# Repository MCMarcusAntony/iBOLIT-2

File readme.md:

--------------------------------------------------------------------------------
New iBolit Simple Diagnostics Cartridge version based on previous work done by
the RBSC group.
--------------------------------------------------------------------------------
- Last 16.07.2022 updates included.
- PCB design converted to KiCAD.
- All parts moved to throught hole to help to begginers build.
- Fuses for all voltages on the top slot.
- Connection to a right hand daughter board added.

- Stop'n'go secondary daughter board design added.

Tools added to this board are:
- Logic probe included on Top three pin connector.
- Lighting and acoustic signals to identify HIGH and LOW status.

Code analisys tools (not properly working yet):
- Stop/Go switch the cpu to stop procesing opcodes.
- Step pushbutton to run just an opcode each time.

Development based on Steve Ciarcia design:

--------------------------------------------------------------------------------
iBolit Simple Diagnostics Cartridge
Copyright (c) 2020-2022 RBSC
Last updated: 16.07.2022
--------------------------------------------------------------------------------

UPDATE from 16.07.2022
----------------------

It's recommended to update the cartridge with an overvoltage protection. See the "iBolit_fuse.jpg" image in the Pics folder!

To install the overvoltage protection, isolate pin 24 of IC1 - cut the traces on both sides of the pin. Then purchase and
solder a 5.1V 1W rated zener diode between pins 12 and 24, the cathode should be connected to pin 24. Solder resettable fuse
0.5A between C2 and pin 24 of IC1. Solder a wire between C5 and the cut off trace to supply power to the voltmeters.

This way the PLD ICs and LEDs will be protected from the overvoltage while the 5V voltmeter will show exact voltage on the slot
connector.

About
-----

iBolit is a simple diagnostics cartridge. During the previous years we've seen numerous messages from MSX users, whose computers
suddenly stopped working after being removed from the storage or after another power cycle. Many people complained about black
screens or about total power failure. It's a known fact that RAM and other elements may go bad during storing or at power-on.
Diagnosing those problems usually starts from checking the power rails, clock signals, reset signal's state and activity on data
and address bus. It has been decided to create a simple diagnostics cartridge that could help to perform the initial check of a
computer and rule out the most common problems.

The cartridge that we named "iBolit" ( see Doctor Aybolit) was created using the GAL22V10 programmable logic chips, LED assemblies
and volt/ammeters from the PC's USB socket tester dongles. There's a cartridge slot installed on the top of iBolit cartridge's
board. There one can insert any cartridge including the one with MSX diagnostics ROM (there are a few, but it would be nice to
create a universal one). The GAL firmware is very primitive - if there's a high level on input, the LED connected to the output
will light up. The cartridge is fairly cheap to build - maximum 12-15 Euro - and is relatively easy to assemble. The daughterboard
with voltmeters is detachable.

Where to buy parts
------------------

The parts for assembling the cartridge can be purchased from these sellers on AliExpress:

 - https://www.aliexpress.com/item/32929139598.html   (buy the one with gray case and USB connectors on the left and right side)
 - https://www.aliexpress.com/item/4000078359420.html (buy 2 converters)
 - https://www.aliexpress.com/item/4001336380255.html (buy 2x5 pin headers)
 - https://www.aliexpress.com/item/32890057619.html   (buy 2x5 pin connectors)
 - https://www.aliexpress.com/item/4000970562846.html (also buy blue and yellow colors)
 - https://www.aliexpress.com/item/32800771545.html   (or use a different 5mm LED)
 - https://www.aliexpress.com/item/32918831775.html   (buy 1kOhm SMD resistor assemblies)
 - https://www.aliexpress.com/item/32948284513.html   (this LED is for the -12v voltmeter)
 - https://www.aliexpress.com/item/32375666910.html   (buy 10uF and 47uF capacitors)
 - https://www.aliexpress.com/item/4001146953252.html (buy 50-pin angled slot connector)

Assembling notes
----------------

Please read the following notes carefully:

 - It's highly recommended to install ceramic capacitors everywhere on the board. For the DC-DC converters the ceramic 10uF
   capacitors are a must

 - To adapt the voltmeters to work with iBolit, you need to first carefully open the USB tester's case with a knife and remove
   the board. Then desolder both indicator panels (mark one indicator panel to know where it came from) and desolder both USB
   connectors from the board. After that solder the indicator panels back to the board, but as low as possible. And finally
   solder two 4-pin pin headers to the board, the pins will have to be forces into the board because the distance between the
   holes is not 2.54mm

 - The voltmeter with a separate red LED is for -12v, it should be installed on the lowest position of the daughterboard. See
   the reference images

 - To install a small red LED to the -12v voltmeter (this step is optional), solder the cathode to the upper GND track and
   anode to the second pin from the top. See the reference images. The LED should be a bit above the voltmeter's board

 - Please note that LED assemblies may have incorrect key position! So please always test the LED assemblies with multimeter
   in the diode testing mode to find the correct polarity. The cathode should be on the right, like marked on the board

 - The pins of both DC-DC converters should be carefully bent at 90 degree angle and the converters have to be installed
   face-down. See the reference images

 - The GAL chips need to be programmed with the firmware before use. A widespread TL866 programmer will do just fine. Use
   the .JED firmware file from the "Firmware" folder and the "GAL22V10D" chip type when programming

 - Instead of one blue and two red LED assemblies you might want to install one red and two blue LED assemblies. Make your
   own choice. It's recommended to install the yellow LED assembly at the rightmost position. If you are installing the
   green LED assembly, you need to select a different value for the resistor assembly, for example 330 Ohm instead of 1kOhm

 - Before inserting the diagnostics board into the MSX slot it's highly recommend to make sure that +5v on the slot is within
   acceptable range (not more than 6-7v!), otherwise the diagnostics board may be damaged. The device doesn't have the
   over-voltage protection on the +5v rail

 - The daughterboard with voltmeters is detachable. When it is detached, no power will be supplied to the upper cartridge slot.
   If you need to use the cartridge slot without the attached daughterboard, you need to put 5 jumpers horizontally on 5 pairs
   of pins of the connector

IMPORTANT!
----------

The RBSC provides all the files and information for free, without any liability (see the disclaimer.txt file). The provided information,
software or hardware must not be used for commercial purposes unless permitted by the RBSC. Producing a small amount of bare boards for
personal projects and selling the rest of the batch is allowed without the permission of RBSC.

When the sources of the tools are used to create alternative projects, please always mention the original source and the copyright!

Contact information
-------------------

The members of RBSC group Tnt23, Wierzbowsky, Pencioner, Ptero, GreyWolf, SuperMax and DJS3000 can be contacted via the group's e-mail
address:

info@rbsc.su

The group's coordinator could be reached via this e-mail address:

admin@rbsc.su

The group's website can be found here:

https://rbsc.su/
https://rbsc.su/ru

The RBSC's hardware repository can be found here:

https://github.com/rbsc

The RBSC's 3D model repository can be found here:

https://www.thingiverse.com/groups/rbsc/things

-= ! MSX FOREVER ! =-

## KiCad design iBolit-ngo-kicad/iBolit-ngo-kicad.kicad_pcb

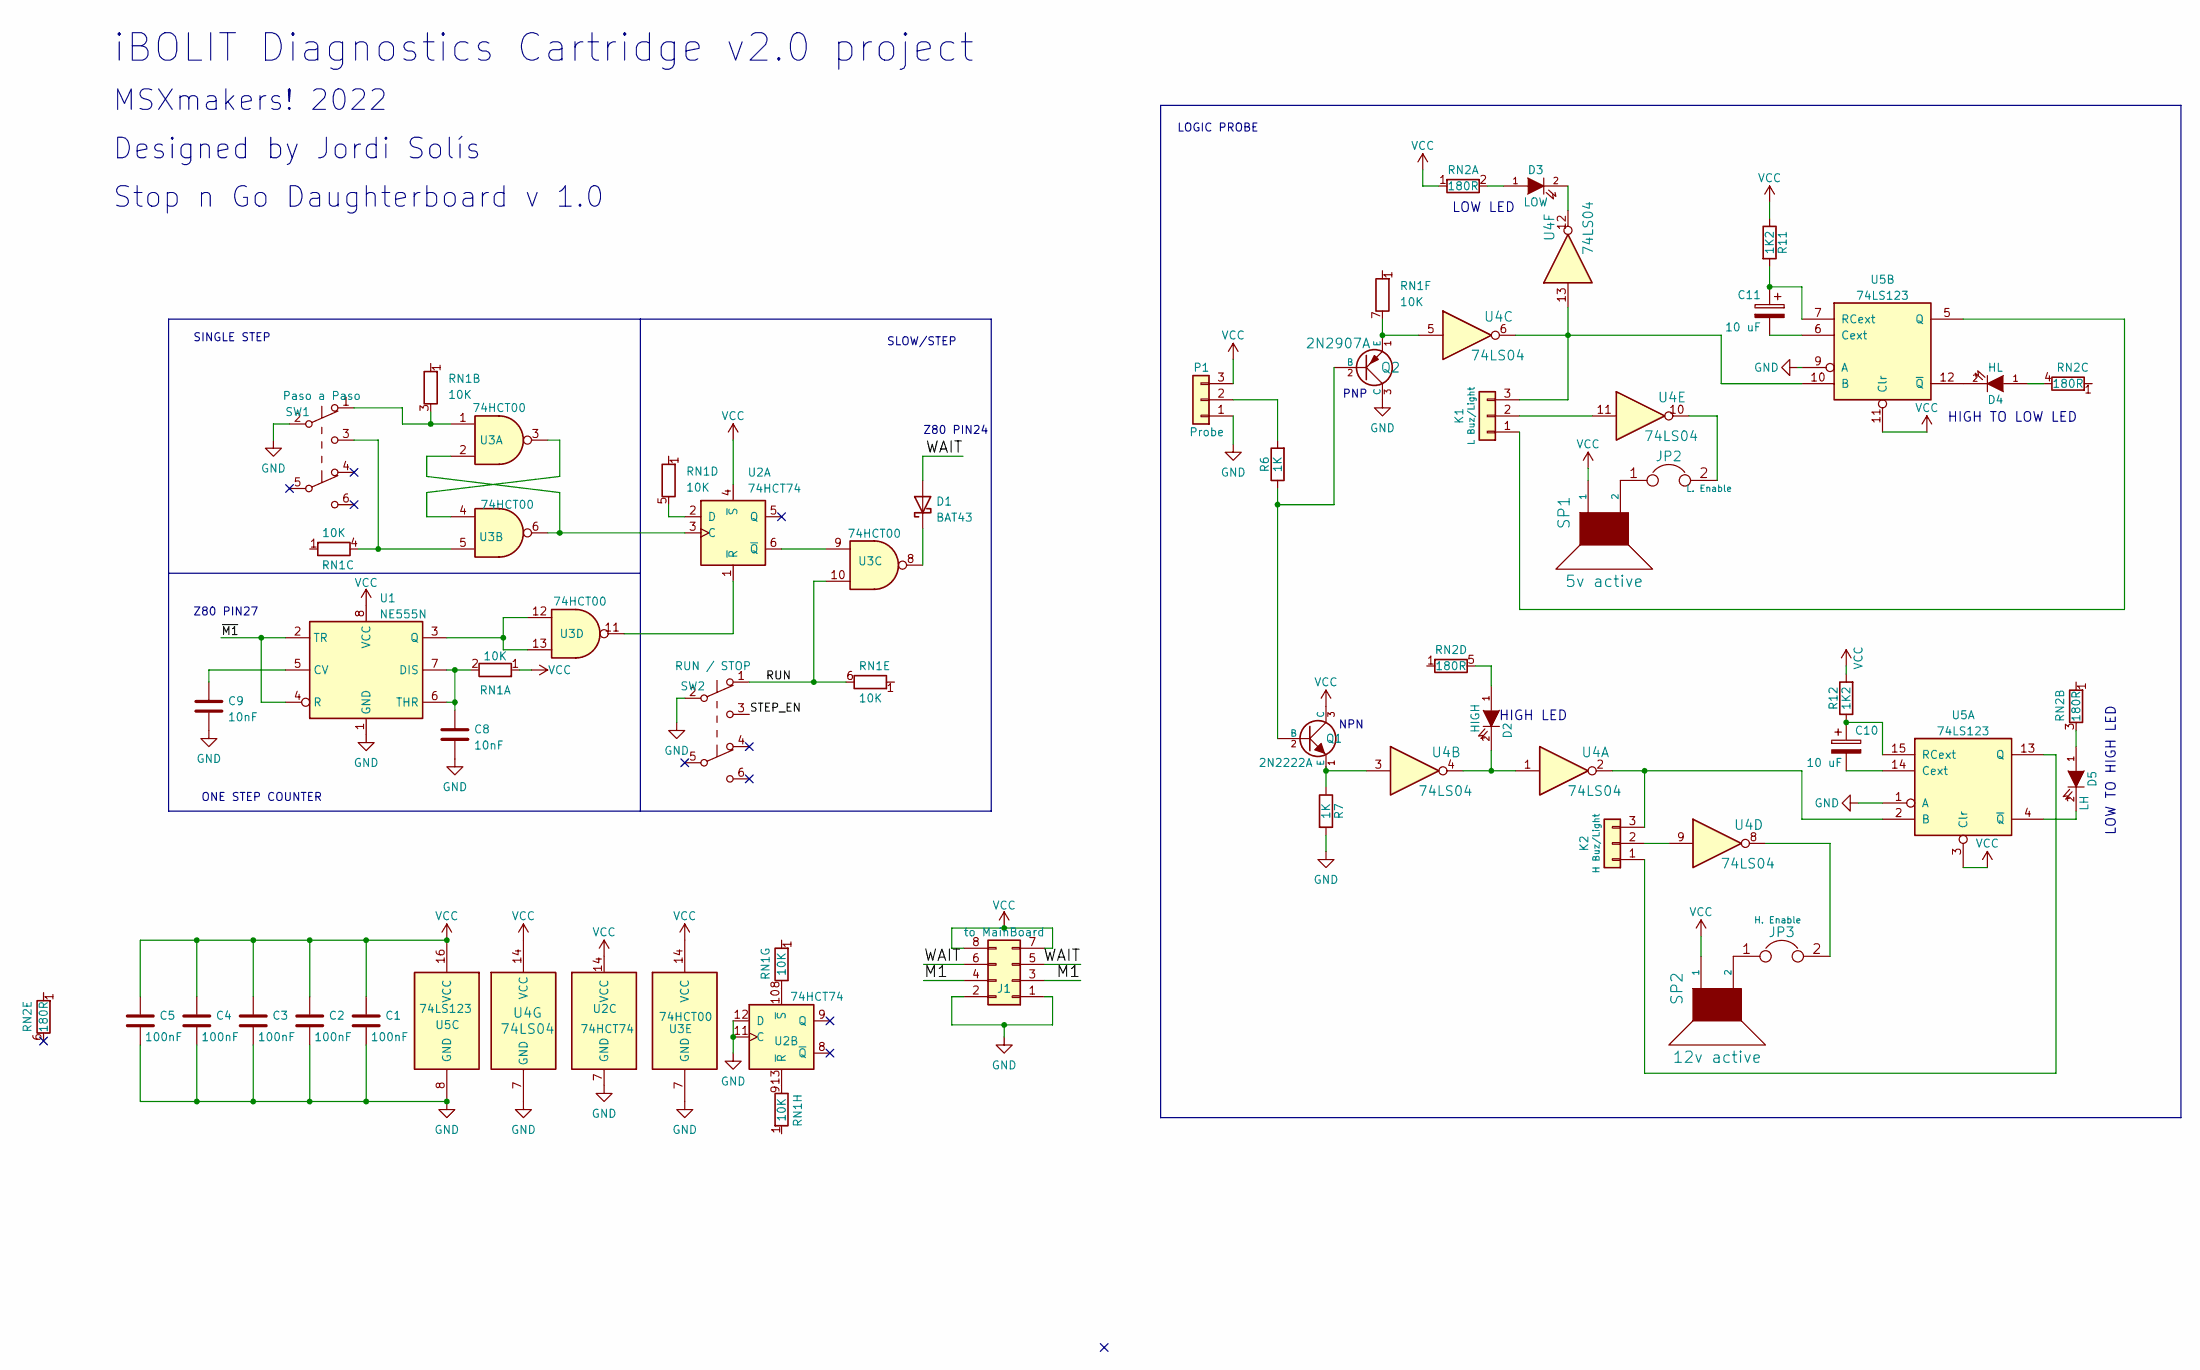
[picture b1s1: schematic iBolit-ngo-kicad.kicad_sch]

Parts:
C1, C2, C3, C4, C5: 100nF; C_Disc_D4.3mm_W1.9mm_P5.00mm
C8, C9: 10nF; C_Disc_D4.3mm_W1.9mm_P5.00mm
C10, C11: 10 uF; CP_Radial_D5.0mm_P2.50mm
D1: BAT43; D_DO-35_SOD27_P7.62mm_Horizontal
D2: HIGH; LED_D3.0mm
D3: LOW; LED_D3.0mm
D4: HL; LED_D3.0mm
D5: LH; LED_D3.0mm
J1: to MainBoard; PinHeader_2x04_P2.54mm_Horizontal
JP2: L. Enable; PinHeader_1x02_P2.54mm_Vertical
JP3: H. Enable; PinHeader_1x02_P2.54mm_Vertical
K1: L Buz/Light; PinHeader_1x03_P2.54mm_Vertical
K2: H Buz/Light; PinHeader_1x03_P2.54mm_Vertical
P1: Probe; PinHeader_1x03_P2.54mm_Vertical
Q1: 2N2222A; TO-92L_Wide
Q2: 2N2907A; TO-92L_Wide
R6, R7: 1K; R_Axial_DIN0207_L6.3mm_D2.5mm_P10.16mm_Horizontal
R11, R12: 1K2; R_Axial_DIN0207_L6.3mm_D2.5mm_P10.16mm_Horizontal
RN1: 10K; R_Array_SIP9
RN2: 180R; R_Array_SIP6
SP1: 5v active; MagneticBuzzer_ProSignal_ABI-009-RC
SP2: 12v active; MagneticBuzzer_ProSignal_ABI-009-RC
SW1: Paso a Paso; SW_Push_2P2T_Toggle_CK_PVA2OAH5xxxxxxV2
SW2: RUN / STOP; SW_Push_2P2T_Toggle_CK_PVA2OAH5xxxxxxV2
U1: NE555N; DIP-8c_W7.62mm_LongPads
U2: 74HCT74; DIP-14c_W7.62mm_LongPads
U3: 74HCT00; DIP-14c_W7.62mm_LongPads
U4: 74LS04; DIP-14c_W7.62mm_LongPads
U5: 74LS123; DIP-16c_W7.62mm_Socket_LongPads

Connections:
/M1: J1.3, J1.4
/RUN: RN1.6 (R5.2), SW1.4 (A), SW2.1 (A), U3.10
/STEP_EN: SW1.5 (B), SW2.3 (C)
/WAIT: D1.2 (A), J1.5, J1.6
/~M1: U1.2 (TR), U1.4 (R)
GND: C1.2, C2.2, C3.2, C4.2, C5.2, C8.2, C9.2, J1.1, J1.2, P1.1, Q2.3 (C), R7.2, SW1.2 (B), SW2.2 (B), U1.1 (GND), U2.7 (GND), U2.11 (C), U2.12 (D), U3.7 (GND), U4.7 (GND), U5.1 (A), U5.8 (GND), U5.9 (A)
unnamed: D1.1 (K), U3.8
unnamed: D2.1 (A), RN2.5 (R4.2)
unnamed: D2.2 (K), U4.1, U4.4
unnamed: D3.1 (A), RN2.2 (R1.2)
unnamed: D3.2 (K), U4.12
unnamed: D4.1 (A), RN2.4 (R3.2)
unnamed: D4.2 (K), U5.12 (~Q)
unnamed: D5.1 (A), RN2.3 (R2.2)
unnamed: D5.2 (K), U5.4 (~Q)
unnamed: JP2.1, SP1.2
unnamed: JP2.2, U4.10
unnamed: JP3.1, SP2.2
unnamed: JP3.2, U4.8
unnamed: K1.1, U5.5 (Q)
unnamed: K1.2, U4.11
unnamed: K1.3, U4.6, U4.13, U5.10 (B)
unnamed: K2.1, U5.13 (Q)
unnamed: K2.2, U4.9
unnamed: K2.3, U4.2, U5.2 (B)
unnamed: P1.2, R6.2
unnamed: Q1.2 (B), Q2.2 (B), R6.1
unnamed: Q1.1 (E), R7.1, U4.3
unnamed: Q2.1 (E), RN1.7 (R6.2), U4.5
unnamed: C8.1, RN1.2 (R1.2), U1.6 (THR), U1.7 (DIS)
unnamed: RN1.3 (R2.2), SW1.1 (A), U3.1
unnamed: RN1.4 (R3.2), SW1.3 (C), U3.5
unnamed: RN1.5 (R4.2), U2.2 (D)
unnamed: C9.1, U1.5 (CV)
unnamed: U1.3 (Q), U3.12, U3.13
unnamed: U2.3 (C), U3.2, U3.6
unnamed: U2.6 (~Q), U3.9
unnamed: U2.1 (~R), U3.11
unnamed: U3.3, U3.4
unnamed: C10.2, U5.14 (Cext)
unnamed: C10.1, R12.1, U5.15 (RCext)
unnamed: C11.2, U5.6 (Cext)
unnamed: C11.1, R11.2, U5.7 (RCext)

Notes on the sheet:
LOGIC PROBE
Stop n Go Daughterboard v 1.0
Designed by Jordi Solís
MSXmakers! 2022
ONE STEP COUNTER
HIGH TO LOW LED
LOW TO HIGH LED
iBOLIT Diagnostics Cartridge v2.0 project
HIGH LED
NPN
Z80 PIN24
SINGLE STEP
LOW LED
PNP
SLOW/STEP
Z80 PIN27

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
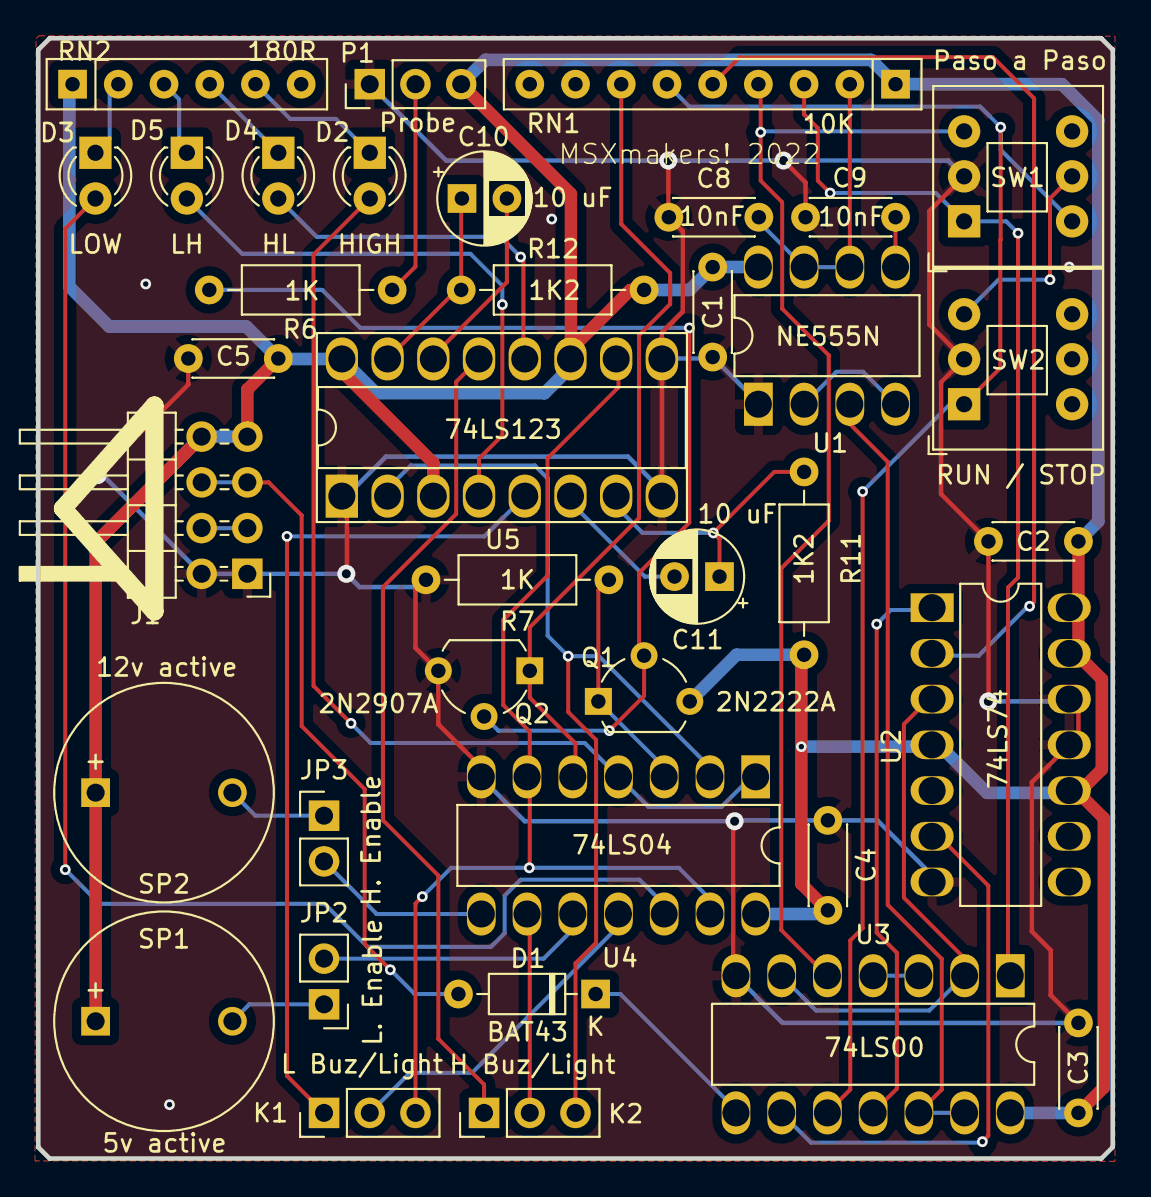
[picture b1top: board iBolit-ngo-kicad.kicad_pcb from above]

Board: 2 copper layers, 59.7 x 62.2 mm, 37 parts (0 on the bottom side), 44 nets.

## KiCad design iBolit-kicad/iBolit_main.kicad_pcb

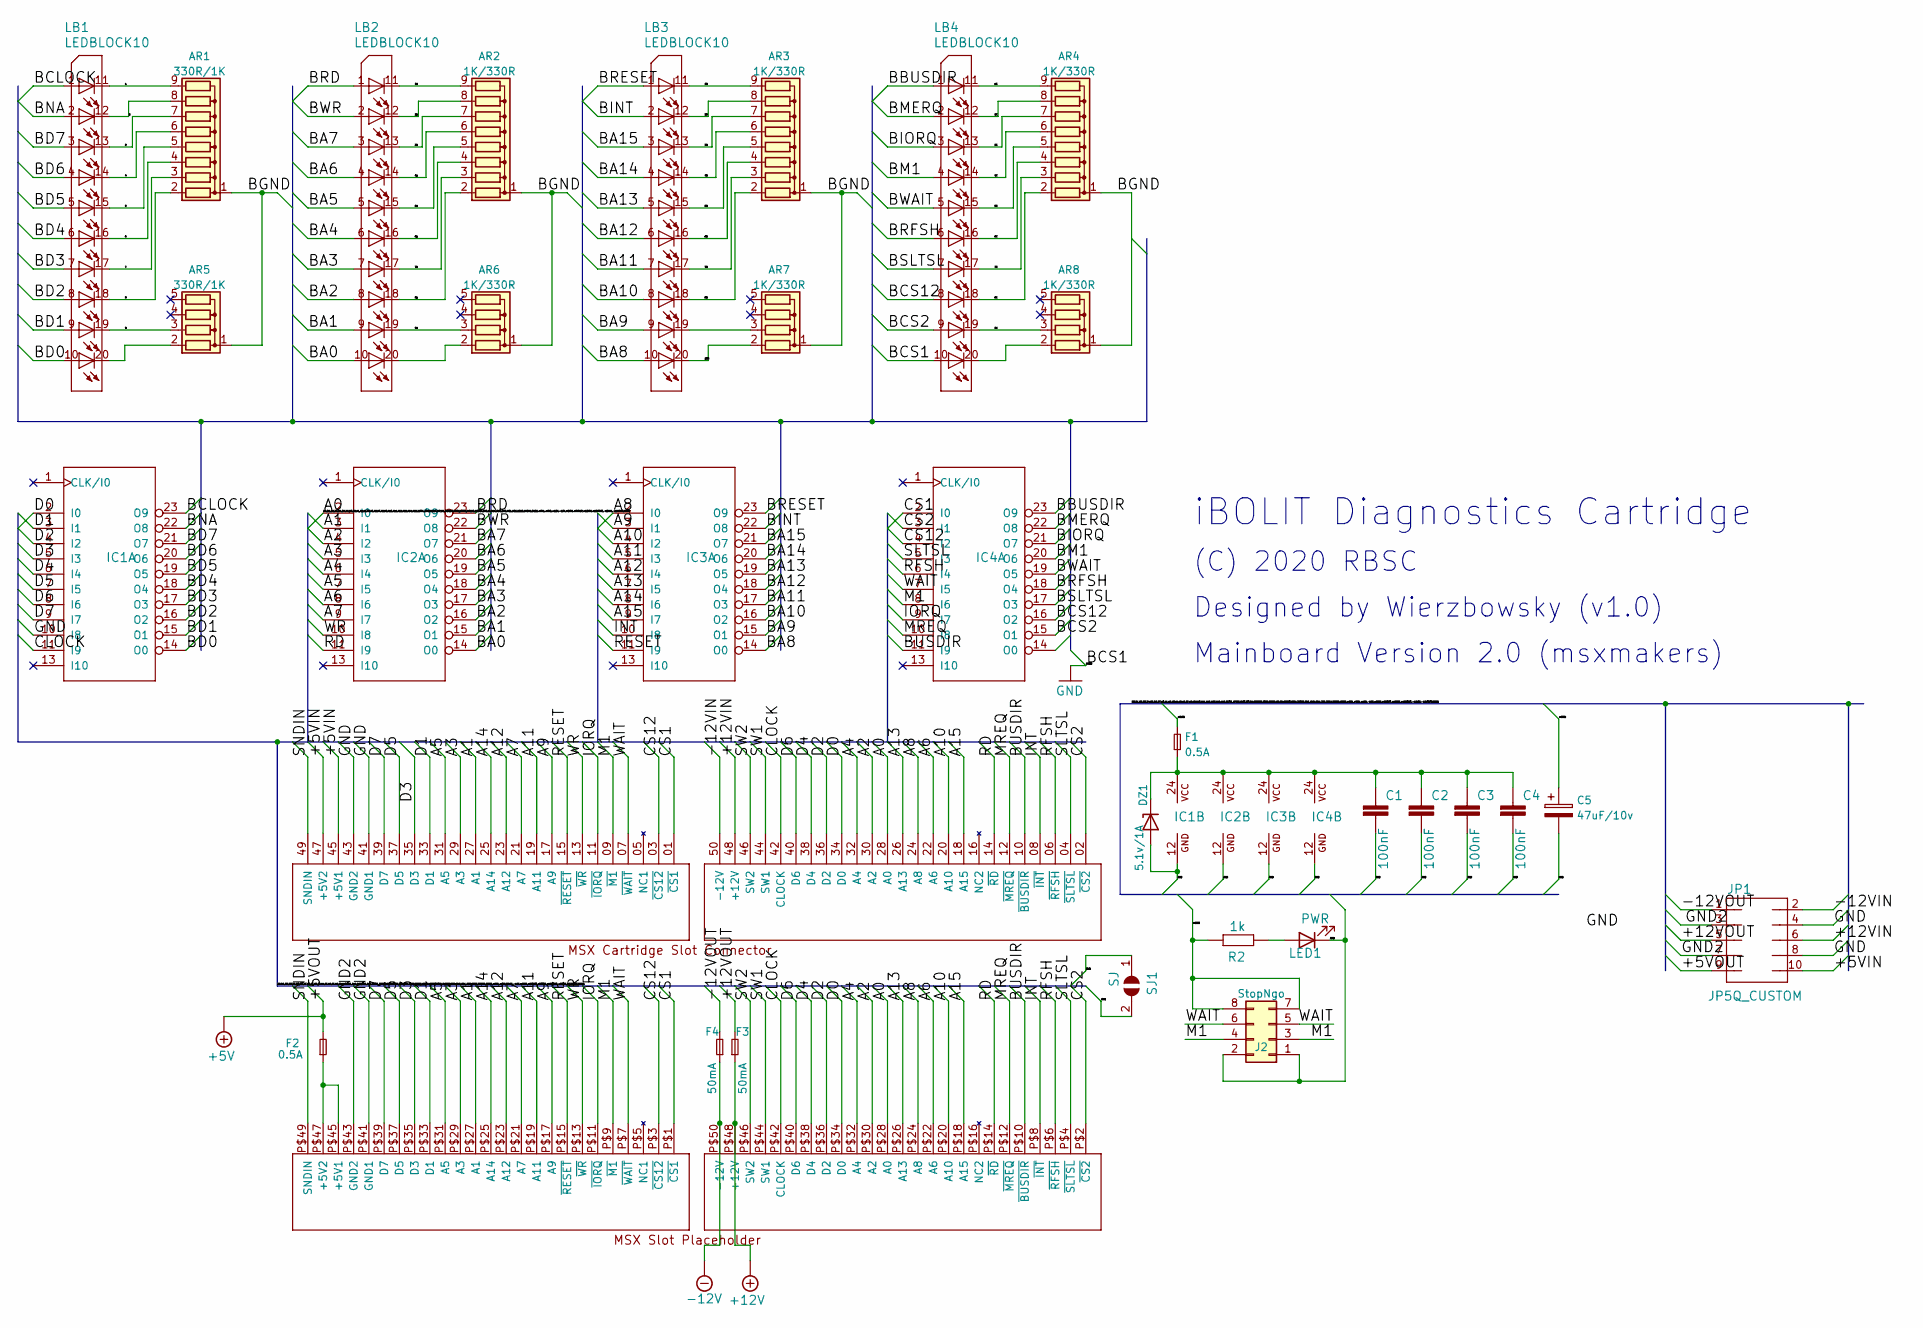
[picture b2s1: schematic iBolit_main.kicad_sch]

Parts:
AR1: 330R/1K; R_Array_SIP9
AR2, AR3, AR4: 1K/330R; R_Array_SIP9
AR5: 330R/1K; R_Array_SIP5
AR6, AR7, AR8: 1K/330R; R_Array_SIP5
C1, C2, C3, C4: 100nF; C_Disc_D4.3mm_W1.9mm_P5.00mm
C5: 47uF/10v; CP_Radial_D6.3mm_P2.50mm
CN1: SLOTCONN; MSX_SLOT_CON
CN2: SLOTPLACEHOLDER; MSX_SLOT_PLP
DZ1: 5.1v/1A; D_DO-41_SOD81_P10.16mm_Horizontal
F1, F2: 0.5A; C_Disc_D5.0mm_W2.5mm_P5.00mm
F3, F4: 50mA; C_Disc_D5.0mm_W2.5mm_P5.00mm
IC1, IC2, IC3, IC4: GAL22V10; DIP-24c_W7.62mm_LongPads
J2: StopNgo; PinSocket_2x04_P2.54mm_Horizontal
JP1: JP5Q_CUSTOM; PinHeader_2x05_P2.54mm_Horizontal
LB1: LEDBLOCK10; HDSP-4832
LB2, LB3: LEDBLOCK10; HDSP-4830
LB4: LEDBLOCK10; HDSP-4850
LED1: PWR; LED_Rectangular_W3.9mm_H1.8mm
R2: 1k; R_Axial_DIN0204_L3.6mm_D1.6mm_P7.62mm_Horizontal
SJ1: SJ; PinHeader_1x02_P2.54mm_Horizontal

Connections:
+5V: F2.2, JP1.9
+12V: CN2.P$48 (+12V), F3.1
-12V: CN2.P$50 (-12V), F4.1
/1: AR1.9 (R8), LB1.11 (L1O)
/1A: AR2.9 (R8), LB2.11 (L1O)
/1B: AR3.9 (R8), LB3.11 (L1O)
/1C: AR4.9 (R8), LB4.11 (L1O)
/2: AR1.8 (R7), LB1.12 (L1O1)
/2A: AR2.8 (R7), LB2.12 (L1O1)
/2B: AR3.8 (R7), LB3.12 (L1O1)
/2C: AR4.8 (R7), LB4.12 (L1O1)
/3: AR1.7 (R6), LB1.13 (L1O2)
/3A: AR2.7 (R6), LB2.13 (L1O2)
/3B: AR3.7 (R6), LB3.13 (L1O2)
/3C: AR4.7 (R6), LB4.13 (L1O2)
/4: AR1.6 (R5), LB1.14 (L1O3)
/4A: AR2.6 (R5), LB2.14 (L1O3)
/4B: AR3.6 (R5), LB3.14 (L1O3)
/4C: AR4.6 (R5), LB4.14 (L1O3)
/5: AR1.5 (R4), LB1.15 (L1O4)
/5A: AR2.5 (R4), LB2.15 (L1O4)
/5B: AR3.5 (R4), LB3.15 (L1O4)
/5C: AR4.5 (R4), LB4.15 (L1O4)
/6: AR1.4 (R3), LB1.16 (L1O5)
/6A: AR2.4 (R3), LB2.16 (L1O5)
/6B: AR3.4 (R3), LB3.16 (L1O5)
/6C: AR4.4 (R3), LB4.16 (L1O5)
/7: AR1.3 (R2), LB1.17 (L1O6)
/7A: AR2.3 (R2), LB2.17 (L1O6)
/7B: AR3.3 (R2), LB3.17 (L1O6)
/7C: AR4.3 (R2), LB4.17 (L1O6)
/8: AR1.2 (R1), LB1.18 (L1O7)
/8A: AR2.2 (R1), LB2.18 (L1O7)
/8B: AR3.2 (R1), LB3.18 (L1O7)
/8C: AR4.2 (R1), LB4.18 (L1O7)
/9: AR5.3 (R2), LB1.19 (L1O8)
/9A: AR6.3 (R2), LB2.19 (L1O8)
/9C: AR8.3 (R2), LB4.19 (L1O8)
/10B: AR7.2 (R1), LB3.20 (L1O9)
/+5VIN: C5.1, CN1.45 (+5V1), CN1.47 (+5V2), F1.2, J2.7, J2.8, JP1.10, R2.2
/+12VIN: CN1.48 (+12V), JP1.6
/+12VOUT: F3.2, JP1.5
/-12VIN: CN1.50 (-12V), JP1.2
/-12VOUT: F4.2, JP1.1
/A0: CN1.28 (A0), CN2.P$28 (A0), IC2.2 (I0)
/A1: CN1.27 (A1), CN2.P$27 (A1), IC2.3 (I1)
/A2: CN1.30 (A2), CN2.P$30 (A2), IC2.4 (I2)
/A3: CN1.29 (A3), CN2.P$29 (A3), IC2.5 (I3)
/A4: CN1.32 (A4), CN2.P$32 (A4), IC2.6 (I4)
/A5: CN1.31 (A5), CN2.P$31 (A5), IC2.7 (I5)
/A6: CN1.22 (A6), CN2.P$22 (A6), IC2.8 (I6)
/A7: CN1.21 (A7), CN2.P$21 (A7), IC2.9 (I7)
/A8: CN1.24 (A8), CN2.P$24 (A8), IC3.2 (I0)
/A9: CN1.17 (A9), CN2.P$17 (A9), IC3.3 (I1)
/A10: CN1.20 (A10), CN2.P$20 (A10), IC3.4 (I2)
/A11: CN1.19 (A11), CN2.P$19 (A11), IC3.5 (I3)
/A12: CN1.23 (A12), CN2.P$23 (A12), IC3.6 (I4)
/A13: CN1.26 (A13), CN2.P$26 (A13), IC3.7 (I5)
/A14: CN1.25 (A14), CN2.P$25 (A14), IC3.8 (I6)
/A15: CN1.18 (A15), CN2.P$18 (A15), IC3.9 (I7)
/BA0: IC2.14 (O0), LB2.10 (L1I9)
/BA1: IC2.15 (O1), LB2.9 (L1I8)
/BA2: IC2.16 (O2), LB2.8 (L1I7)
/BA3: IC2.17 (O3), LB2.7 (L1I6)
/BA4: IC2.18 (O4), LB2.6 (L1I5)
/BA5: IC2.19 (O5), LB2.5 (L1I4)
/BA6: IC2.20 (O6), LB2.4 (L1I3)
/BA7: IC2.21 (O7), LB2.3 (L1I2)
/BA8: IC3.14 (O0), LB3.10 (L1I9)
/BA9: IC3.15 (O1), LB3.9 (L1I8)
/BA10: IC3.16 (O2), LB3.8 (L1I7)
/BA11: IC3.17 (O3), LB3.7 (L1I6)
/BA12: IC3.18 (O4), LB3.6 (L1I5)
/BA13: IC3.19 (O5), LB3.5 (L1I4)
/BA14: IC3.20 (O6), LB3.4 (L1I3)
/BA15: IC3.21 (O7), LB3.3 (L1I2)
/BBUSDIR: IC4.23 (O9), LB4.1 (L1I)
/BCLOCK: IC1.23 (O9), LB1.1 (L1I)
/BCS2: IC4.15 (O1), LB4.9 (L1I8)
/BCS12: IC4.16 (O2), LB4.8 (L1I7)
/BD0: IC1.14 (O0), LB1.10 (L1I9)
/BD1: IC1.15 (O1), LB1.9 (L1I8)
/BD2: IC1.16 (O2), LB1.8 (L1I7)
/BD3: IC1.17 (O3), LB1.7 (L1I6)
/BD4: IC1.18 (O4), LB1.6 (L1I5)
/BD5: IC1.19 (O5), LB1.5 (L1I4)
/BD6: IC1.20 (O6), LB1.4 (L1I3)
/BD7: IC1.21 (O7), LB1.3 (L1I2)
/BINT: IC3.22 (O8), LB3.2 (L1I1)
/BIORQ: IC4.21 (O7), LB4.3 (L1I2)
/BM1: IC4.20 (O6), LB4.4 (L1I3)
/BMERQ: IC4.22 (O8), LB4.2 (L1I1)
/BNA: IC1.22 (O8), LB1.2 (L1I1)
/BRD: IC2.23 (O9), LB2.1 (L1I)
/BRESET: IC3.23 (O9), LB3.1 (L1I)
/BRFSH: IC4.18 (O4), LB4.6 (L1I5)
/BSLTSL: IC4.17 (O3), LB4.7 (L1I6)
/BUSDIR: CN1.10 (~BUSDIR), CN2.P$10 (~BUSDIR), IC4.11 (I9)
/BWAIT: IC4.19 (O5), LB4.5 (L1I4)
/BWR: IC2.22 (O8), LB2.2 (L1I1)
/CLOCK: CN1.42 (CLOCK), CN2.P$42 (CLOCK), IC1.11 (I9)
/CS1: CN1.01 (~CS1), CN2.P$1 (~CS1), IC4.2 (I0)
/CS2: CN1.02 (~CS2), CN2.P$2 (~CS2), IC4.3 (I1)
/CS12: CN1.03 (~CS12), CN2.P$3 (~CS12), IC4.4 (I2)
/D0: CN1.34 (D0), CN2.P$34 (D0), IC1.2 (I0)
/D1: CN1.33 (D1), CN2.P$33 (D1), IC1.3 (I1)
/D2: CN1.36 (D2), CN2.P$36 (D2), IC1.4 (I2)
/D3: CN1.35 (D3), CN2.P$35 (D3), IC1.5 (I3)
/D4: CN1.38 (D4), CN2.P$38 (D4), IC1.6 (I4)
/D5: CN1.37 (D5), CN2.P$37 (D5), IC1.7 (I5)
/D6: CN1.40 (D6), CN2.P$40 (D6), IC1.8 (I6)
/D7: CN1.39 (D7), CN2.P$39 (D7), IC1.9 (I7)
/GND2: CN2.P$41 (GND1), CN2.P$43 (GND2), JP1.3, JP1.7
/INT: CN1.08 (~INT), CN2.P$8 (~INT), IC3.10 (I8)
/IORQ: CN1.11 (~IORQ), CN2.P$11 (~IORQ), IC4.9 (I7)
/M1: CN1.09 (~M1), CN2.P$9 (~M1), IC4.8 (I6), J2.3, J2.4
/MREQ: CN1.12 (~MREQ), CN2.P$12 (~MREQ), IC4.10 (I8)
/RD: CN1.14 (~RD), CN2.P$14 (~RD), IC2.11 (I9)
/RESET: CN1.15 (~RESET), CN2.P$15 (~RESET), IC3.11 (I9)
/RFSH: CN1.06 (~RFSH), CN2.P$6 (~RFSH), IC4.6 (I4)
/SLTSL: CN1.04 (~SLTSL), CN2.P$4 (~SLTSL), IC4.5 (I3)
/SNDIN: CN1.49 (SNDIN), CN2.P$49 (SNDIN)
/SW1: CN1.44 (SW1), CN2.P$44 (SW1), SJ1.2
/SW2: CN1.46 (SW2), CN2.P$46 (SW2), SJ1.1
/WAIT: CN1.07 (~WAIT), CN2.P$7 (~WAIT), IC4.7 (I5), J2.5, J2.6
/WR: CN1.13 (~WR), CN2.P$13 (~WR), IC2.10 (I8)
GND: AR1.1 (common), AR2.1 (common), AR3.1 (common), AR4.1 (common), AR5.1 (common), AR6.1 (common), AR7.1 (common), AR8.1 (common), C1.2, C2.2, C3.2, C4.2, C5.2, CN1.41 (GND1), CN1.43 (GND2), DZ1.2 (A), IC1.10 (I8), IC1.12 (GND), IC2.12 (GND), IC3.12 (GND), IC4.12 (GND), J2.1, J2.2, JP1.4, JP1.8, LB4.10 (L1I9), LED1.1 (K)
unnamed: AR5.2 (R1), LB1.20 (L1O9)
unnamed: AR6.2 (R1), LB2.20 (L1O9)
unnamed: AR7.3 (R2), LB3.19 (L1O8)
unnamed: AR8.2 (R1), LB4.20 (L1O9)
unnamed: C1.1, C2.1, C3.1, C4.1, DZ1.1 (K), F1.1, IC1.24 (VCC), IC2.24 (VCC), IC3.24 (VCC), IC4.24 (VCC)
unnamed: CN2.P$45 (+5V1), CN2.P$47 (+5V2), F2.1
unnamed: LED1.2 (A), R2.1

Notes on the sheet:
(C) 2020 RBSC
Mainboard Version 2.0 (msxmakers)
Designed by Wierzbowsky (v1.0)
iBOLIT Diagnostics Cartridge

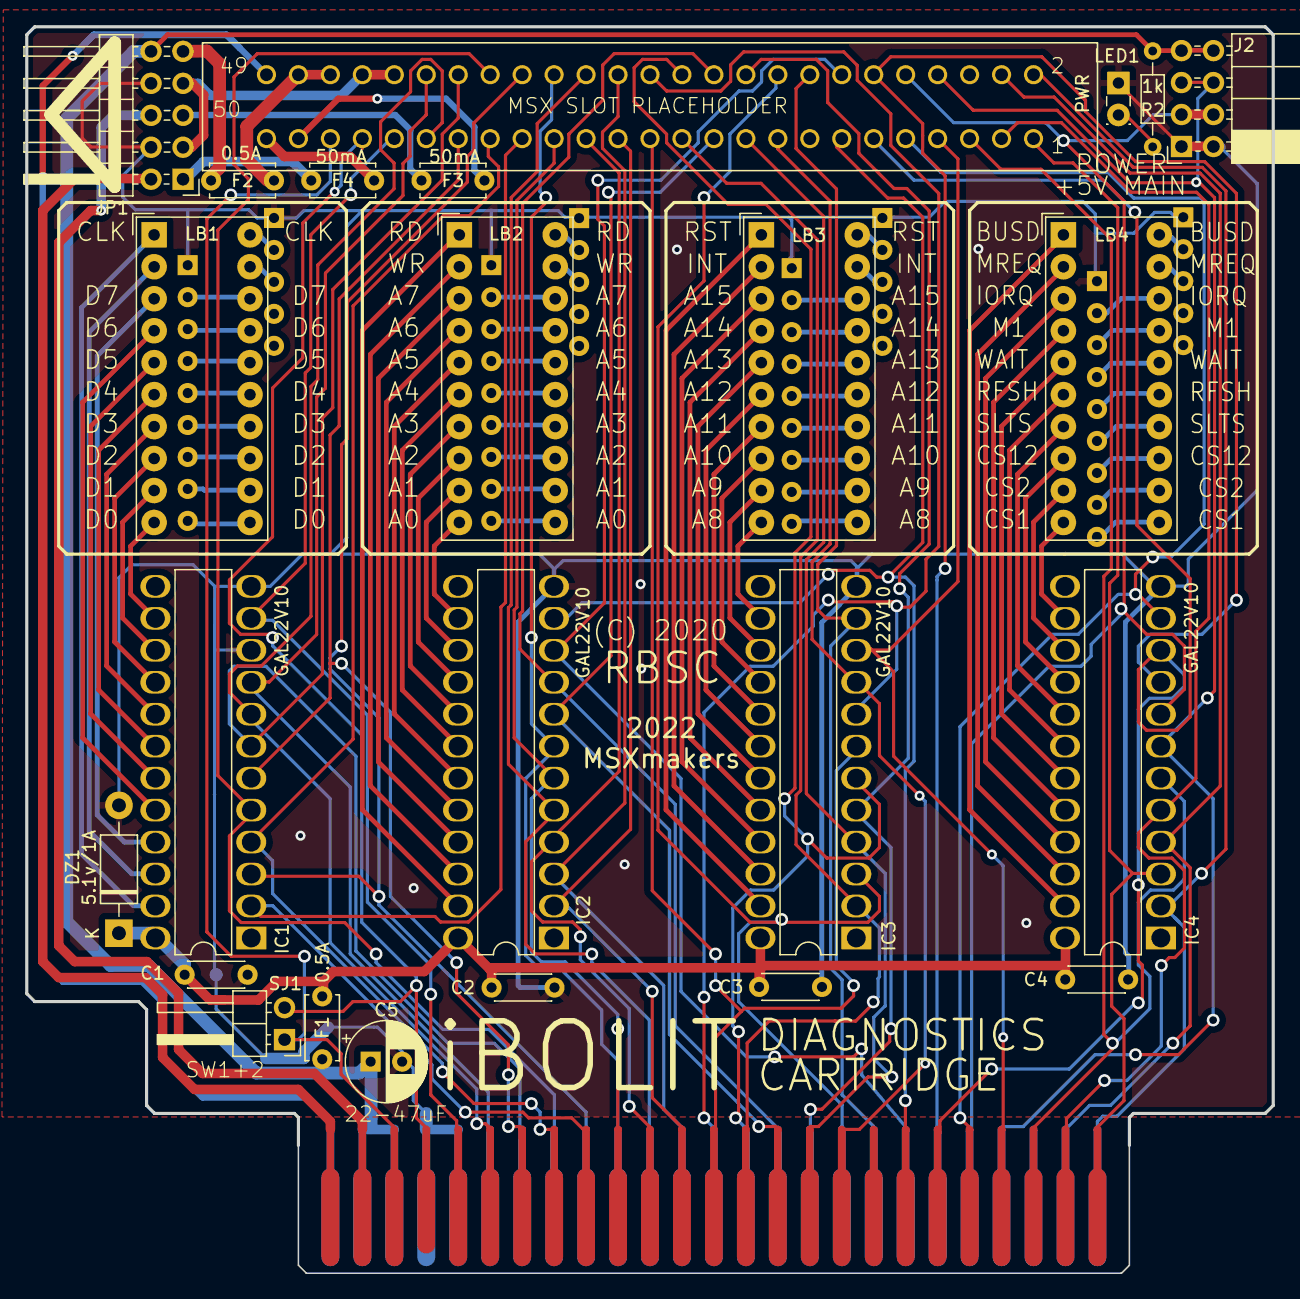
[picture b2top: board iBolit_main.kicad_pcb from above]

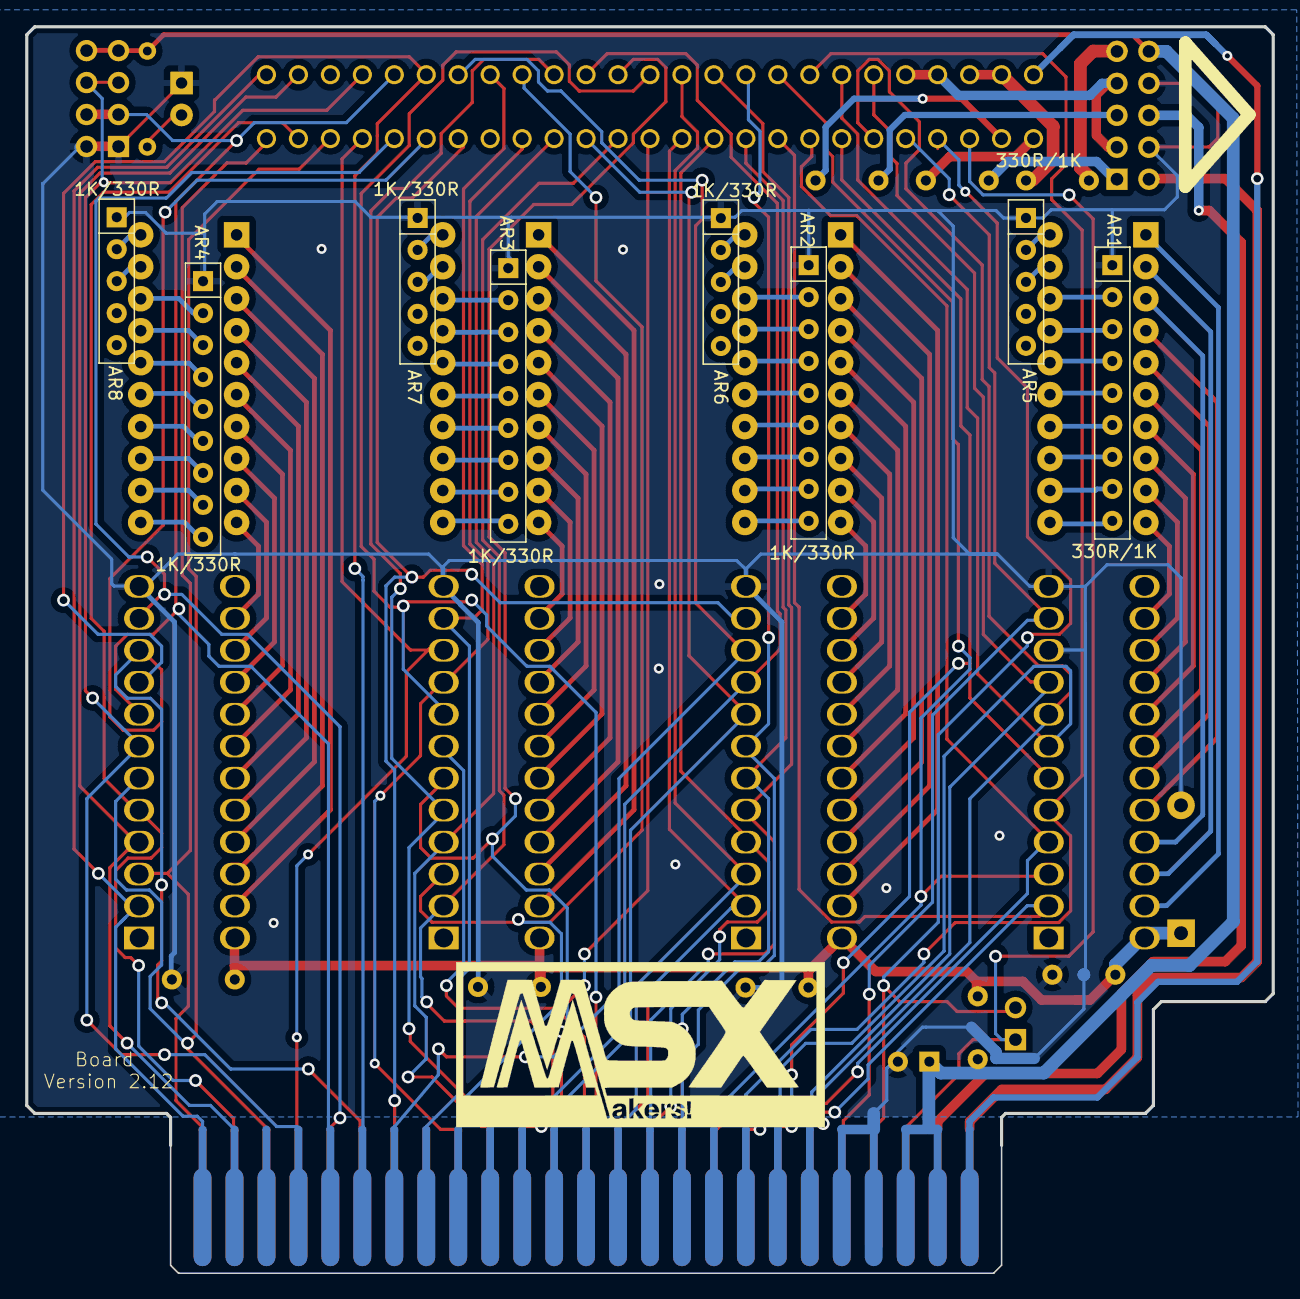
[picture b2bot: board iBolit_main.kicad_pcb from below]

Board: 2 copper layers, 99.1 x 99.1 mm, 33 parts (8 on the bottom side), 134 nets.

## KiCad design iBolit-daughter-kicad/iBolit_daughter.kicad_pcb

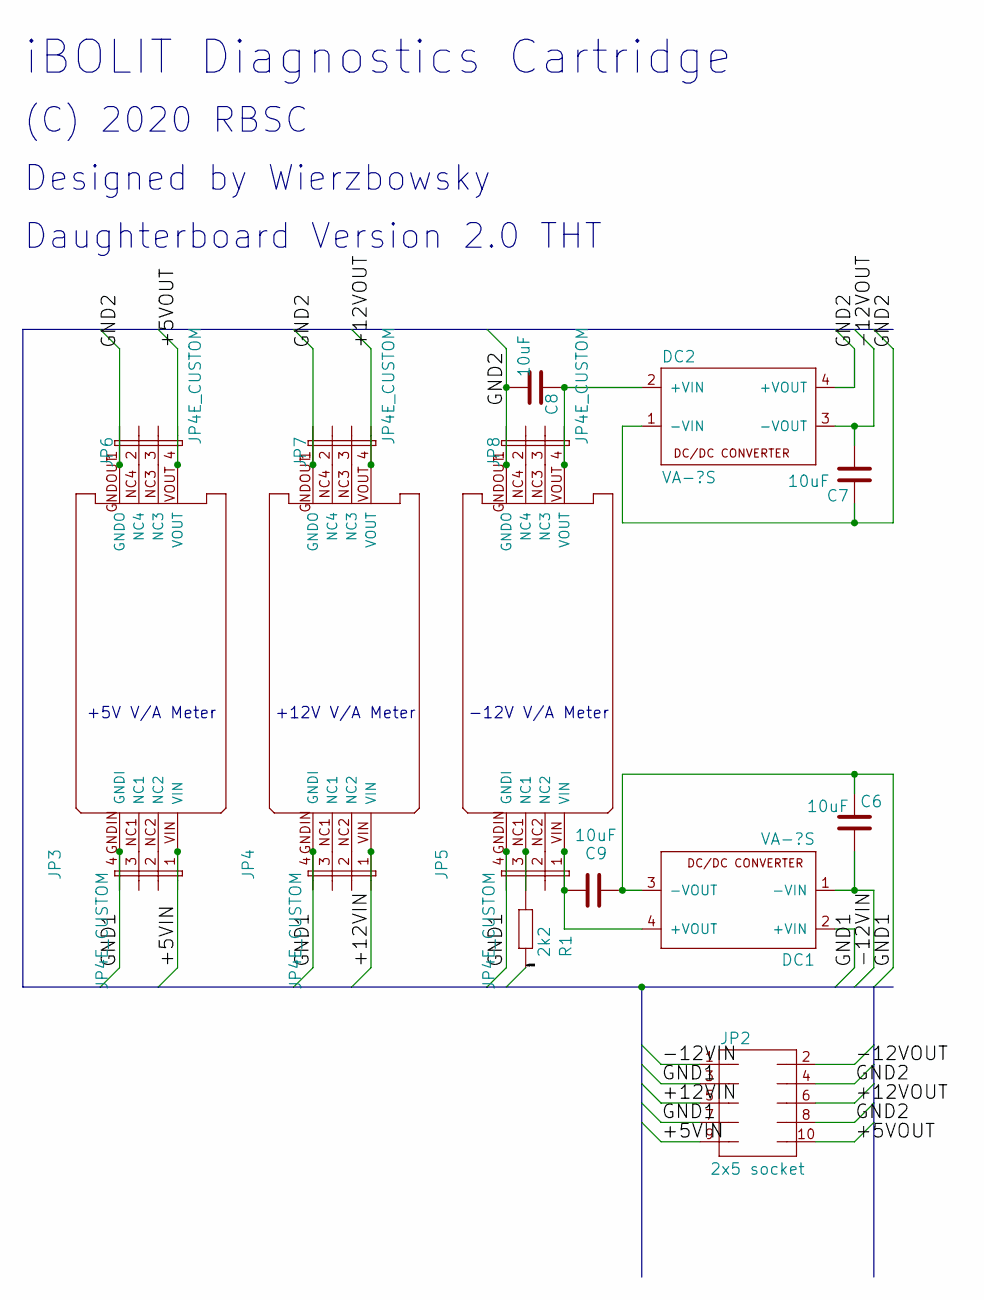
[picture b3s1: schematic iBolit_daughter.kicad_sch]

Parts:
C6, C7, C8, C9: 10uF; C_Disc_D4.7mm_W2.5mm_P5.00mm
DC1, DC2: VA-?S; 4SIL
JP2: 2x5 socket; JP5Q_CUSTOM
JP3, JP4, JP5, JP6, JP7, JP8: JP4E_CUSTOM; JP4_CUSTOM
R1: 2k2; R_Axial_DIN0207_L6.3mm_D2.5mm_P7.62mm_Horizontal
X1, X2, X3: VA-METER; VA_METER

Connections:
/+5VIN: JP2.9, JP3.1, R1.1, X1.VIN
/+5VOUT: JP2.10, JP6.4, X1.VOUT
/+12VIN: JP2.5, JP4.1, X2.VIN
/+12VOUT: JP2.6, JP7.4, X2.VOUT
/-12VIN: C6.2, DC1.1 (-VIN), JP2.1
/-12VOUT: C7.2, DC2.3 (-VOUT), JP2.2
/GND1: C6.1, C9.2, DC1.2 (+VIN), DC1.3 (-VOUT), JP2.3, JP2.7, JP3.4, JP4.4, JP5.4, X1.GNDIN (GNDI), X2.GNDIN (GNDI), X3.GNDIN (GNDI)
/GND2: C7.1, C8.2, DC2.1 (-VIN), DC2.4 (+VOUT), JP2.4, JP2.8, JP6.1, JP7.1, JP8.1, X1.GNDOUT (GNDO), X2.GNDOUT (GNDO), X3.GNDOUT (GNDO)
unnamed: C8.1, DC2.2 (+VIN), JP8.4, X3.VOUT
unnamed: JP3.2, X1.NC2
unnamed: JP3.3, X1.NC1
unnamed: JP4.2, X2.NC2
unnamed: JP4.3, X2.NC1
unnamed: C9.1, DC1.4 (+VOUT), JP5.1, X3.VIN
unnamed: JP5.2, X3.NC2
unnamed: JP5.3, R1.2, X3.NC1
unnamed: JP6.2, X1.NC4
unnamed: JP6.3, X1.NC3
unnamed: JP7.2, X2.NC4
unnamed: JP7.3, X2.NC3
unnamed: JP8.2, X3.NC4
unnamed: JP8.3, X3.NC3

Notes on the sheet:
iBOLIT Diagnostics Cartridge
Daughterboard Version 2.0 THT
+12V V/A Meter
+5V V/A Meter
(C) 2020 RBSC
Designed by Wierzbowsky
-12V V/A Meter

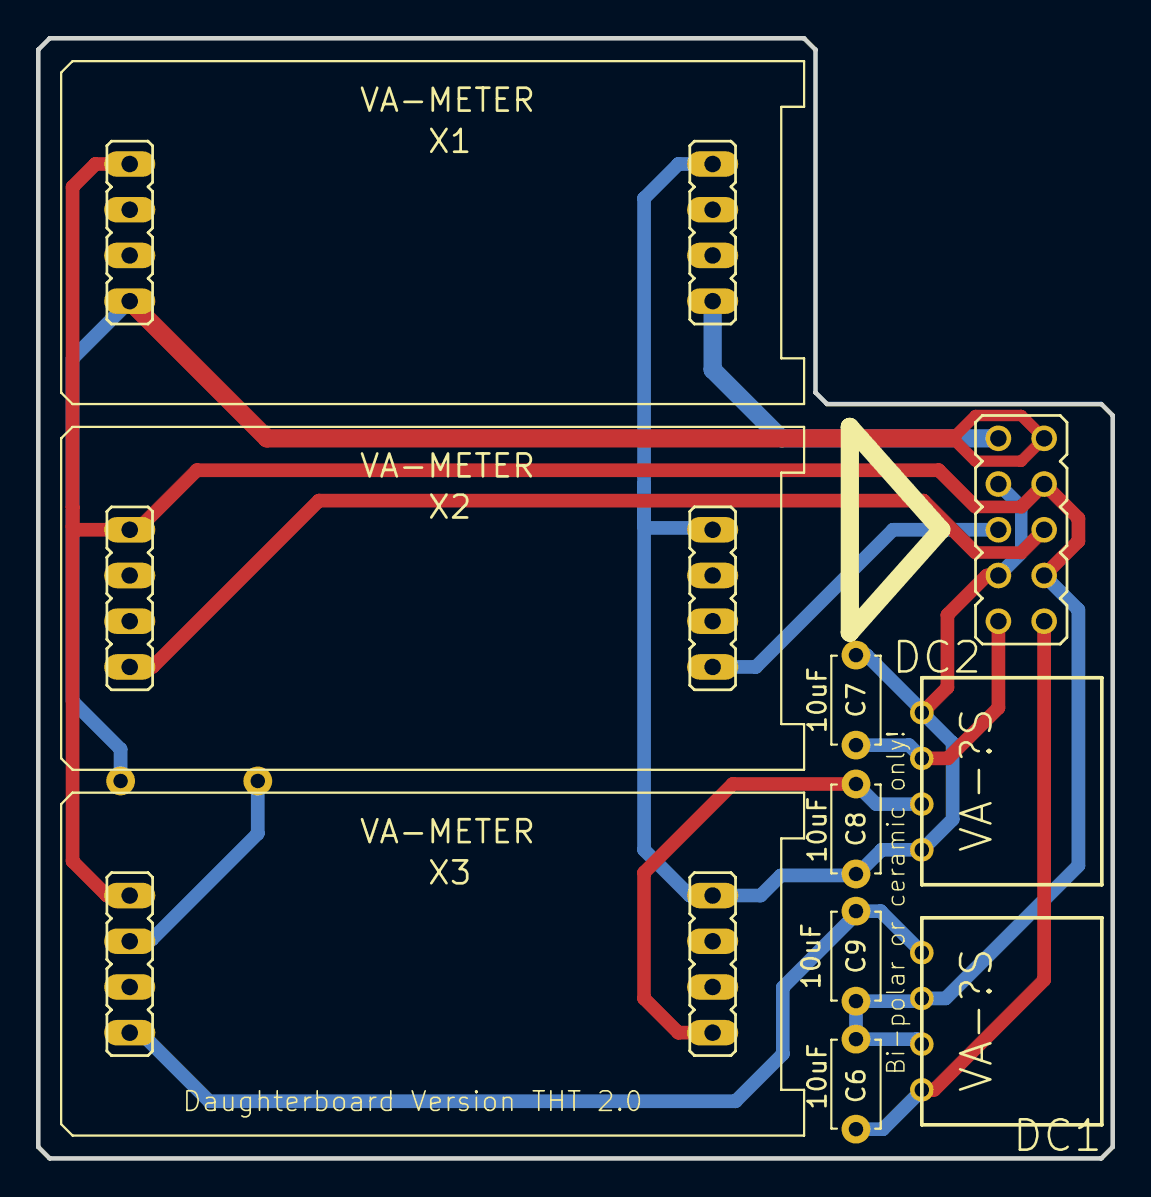
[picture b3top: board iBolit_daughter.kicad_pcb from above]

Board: 2 copper layers, 59.7 x 62.2 mm, 17 parts (1 on the bottom side), 22 nets.

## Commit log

2024-04-06 Update readme.txt
    adding new version
2024-04-06 rollback readme.txt
